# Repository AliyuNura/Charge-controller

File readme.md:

This is a solar charge controller to charge 12V battery with a solar panel of up to 200Watt

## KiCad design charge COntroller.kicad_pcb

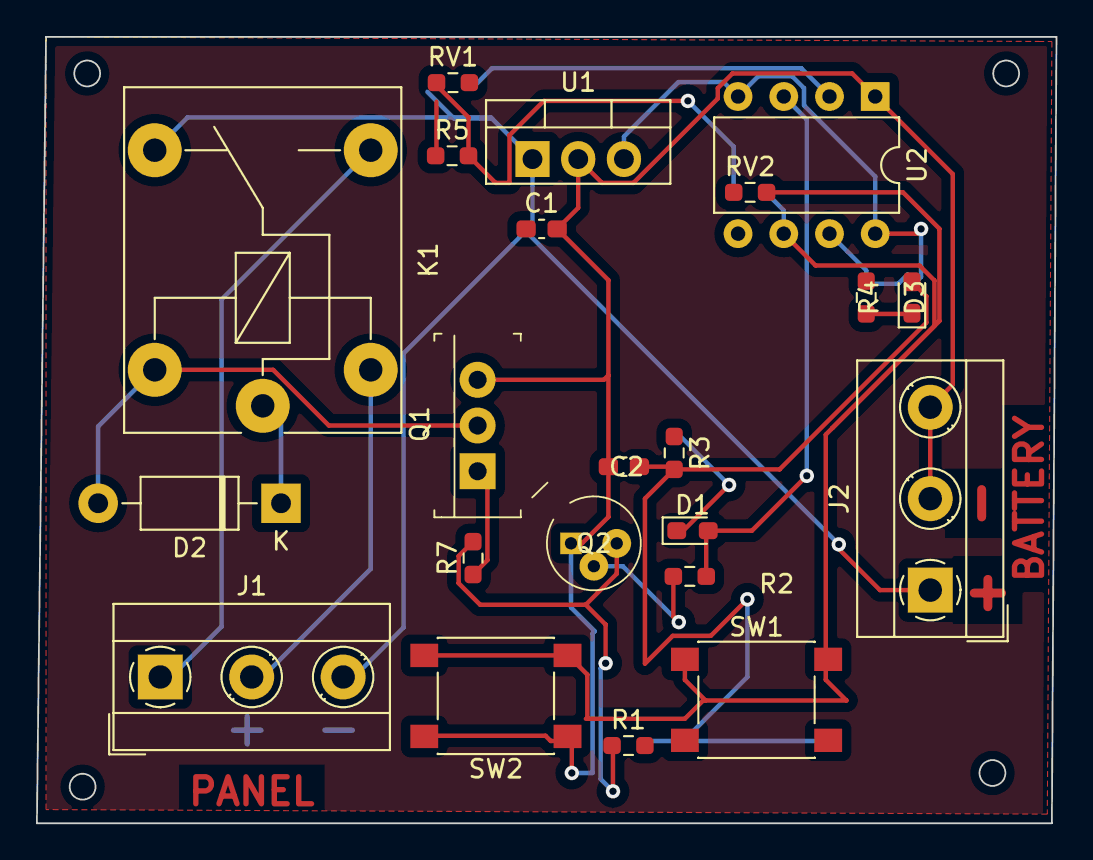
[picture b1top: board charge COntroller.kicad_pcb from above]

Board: 2 copper layers, 56.6 x 43.7 mm, 22 parts (0 on the bottom side), 17 nets.

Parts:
C1, C2: C; C_0603_1608Metric_Pad1.08x0.95mm_HandSolder
D1, D3: LED; LED_0603_1608Metric_Pad1.05x0.95mm_HandSolder
D2: 1N4007; D_DO-41_SOD81_P10.16mm_Horizontal
J1, J2: 282834-3; TerminalBlock_MetzConnect_Type101_RT01603HBWC_1x03_P5.08mm_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
K1: FINDER-36.11; Relay_SPDT_Finder_36.11
Q1: IRF540NPBF; TO-220-3
Q2: 2N2222; TO-18-3
R1, R5: 330; R_0603_1608Metric_Pad0.98x0.95mm_HandSolder
R2, R3, R4: 1K; R_0603_1608Metric_Pad0.98x0.95mm_HandSolder
R7: 100; R_0603_1608Metric_Pad0.98x0.95mm_HandSolder
RV1, RV2: 10K; R_0603_1608Metric_Pad0.98x0.95mm_HandSolder
SW1, SW2: SW; SW_SPST_PTS645
U1: LM7805_TO220; TO-220-3_Vertical
U2: NE555P; DIP-8_W7.62mm

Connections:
+VE IN: J1.2, K1.A1
/Q: D1.2 (A), R2.1, U2.3 (Q)
/R: C2.1, D3.2 (A), R1.2, R3.2, SW1.2, U1.3 (VO), U2.4 (R), U2.8 (VCC)
/THR: RV2.2, SW1.1, SW2.2, U2.6 (THR)
/TR: RV1.2, U2.2 (TR)
BATTERY +VE: C1.1, J1.3, J2.1, K1.12, R5.1, U1.1 (VI)
DUMP: J1.1, K1.14
GND: C1.2, C2.2, J2.2, J2.3, Q1.3 (S), Q2.1 (E), SW2.1, U1.2 (GND), U2.1 (GND)
unnamed: D1.1 (K), R3.1
unnamed: D2.2 (A), K1.A2, Q1.2 (D)
unnamed: D2.1 (K), K1.11
unnamed: D3.1 (K), R4.2
unnamed: Q1.1 (G), R7.1
unnamed: Q2.2 (B), R2.2
unnamed: Q2.3 (C), R1.1, R7.2
unnamed: R5.2, RV1.1, RV2.1
unnamed: R4.1, U2.7 (DIS)

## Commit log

2022-09-13 charge controller
2022-09-13 adding a readme
